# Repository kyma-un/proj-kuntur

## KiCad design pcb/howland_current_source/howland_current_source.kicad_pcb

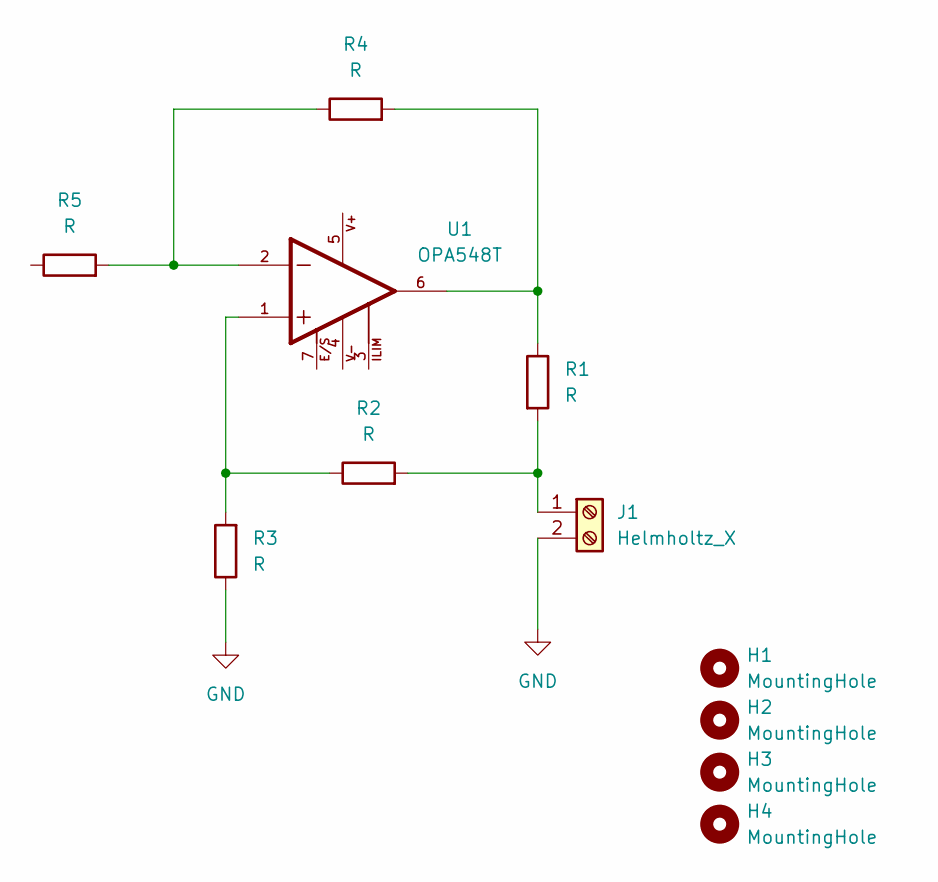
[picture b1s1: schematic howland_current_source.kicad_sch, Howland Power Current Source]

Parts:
H1, H2, H3, H4: MountingHole; MountingHole_4.3mm_M4_ISO14580_Pad
J1: Helmholtz_X; TerminalBlock_Phoenix_PT-1,5-2-3.5-H_1x02_P3.50mm_Horizontal
R1: R; R_Axial_DIN0922_L20.0mm_D9.0mm_P25.40mm_Horizontal
R2, R3, R4, R5: R; R_1206_3216Metric
U1: OPA548T; TO127P1016X449X2137-7; PARTREV 01/03

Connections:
GND: J1.2, R3.1
unnamed: J1.1, R1.2, R2.2
unnamed: R1.1, R4.2, U1.6
unnamed: R2.1, R3.2, U1.1
unnamed: R4.1, R5.2, U1.2

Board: 2 copper layers, 11 parts (0 on the bottom side), 5 nets, no tracks yet.
